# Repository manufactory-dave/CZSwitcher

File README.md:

# CZSwitcher

====Cube Zero Switcher Project Version 2 Alpha====

Version 2 alpha
Board revisions:

Distro Rev [tbc]
Carriage Rev [tbc]
Tool Rev [tbc]

====Changelog====

[fix V1 errors]
Add ADXL345 to carriage board
Upgrade files to KiCad V6
Integrate files into one project [maybe]

====Cube Zero Overview====

Cube Zero is a CoreXY tool changing 3D printer design that is currently WIP. The requirements for the machine are:
- The machine shall have high rigidity
- The machine should be readily adaptable to use a heated enclosure
- The machine must be electrically safe
- The machine must use CoreXY architecture
- The design should minimise moving mass
- The machine shall support multi-material prints
- The machine should have rapidly changeable tools to enable rapid swap reliability
- The machine should not be reliant on a specific firmware

These requirements have evolved with the design, currently the design is a CoreXY machine with 3 tool changer stations. Currently the design utilises direct drive extruders using Nema10 motors and a worm gear arrangement to minimise mass. Hot end compatibiliy is to be E3D groovemount.

Why choose the name Cube Zero? Because that film came after Cube 2 Hypercube, and it was a better film.

====Custom Electronics Overview (This repository)====

The drive to minimise mass (and the potential for tangling with 3 or more tools all with separate cable trains to be independently strain relieved and managed leads to the chosen solution: Independent wiring to tool storage bays and the toolhead, with a single flexible flat cable (FFC) connecting the toolhead.
A wide FFC is capable of supporting its own mass and is very light, and furthermore is flexible in two axis simultaneously, making it substantially simpler and more robust than multiple cable chains, at the cost of requiring breakout PCBs.
By selecting a suitably heavy duty FFC (Samtec manufacture high current capacity cables) and using multiple conductors for the heater, 5A current capacity for heaters is easily achieved.
The result of using hot swapped tools is that a single stepper driver can be  used to control every extruder, meaning that any 4 driver board could theoretically handle an arbitrary number of tools.

The system architecture creates the need for several circuit boards having the following requirements:
- The electronics must connect the printer control board to the docking stations and toolhead
- Sensor, motor and heater connections should be switched in a low latency, low resistance manner
- Tool docks must have temperature sense and heater connections
- The toolhead should support auxilliary functions such as part cooling fans, servo motors and bed levelling sensors
- The toolhead should support ADXL345 integration for Klipper Input Shaper operation

[edited up to here]

Three seperate KiCad v5 projects are stored here:

Distroboard: The heart of the electronics - this takes a common stepper motor input and 3 separate fan/heater/thermistor channels, bed probing and well as 3 auxilliary channels and routes them to a 20 way 1mm pitch FFC.
Designed to interface with a Bigtreetech GTR V1.0, but will probably work with other boards, YMMV.

*Current Ratings*
Heaters - 3.5A per channel, max 30V
Fans - 1A per channel, routed via Aux 1
Auxilliary channels - 1A per channel, max 24V
Thermistors - currently designed to interface directly with the GTR thermistors. A 3V3 connection is required for at least one thermistor as this supplies power to your Z probe solution of choice.
	Provision has been made to allow these channels to drive thermocouple or PTH amplifiers.
5V in - 1A max
VDC in - 1A max, 30V max
Stepper motor - designed for a TMC2209, with protection circuitry for hot swapping taken from the TMC2209 datasheet. This is not intended and disable stepper commands should be used before swapping motors, however the protection is there just in case.
Probe - low current.

Carriageboard: 3 separate boards.

Carriage Board A:
Breaks out the FFC cable into the 3 aux outputs, a BLTouch connector, an interface for a Precision Piezo V2.85 board and 2 piezo inputs, status LEDs for the heater and probe throughput.

Carriage Board B:
Interfaces with toolhead, provides 2 aux outputs, and repeats status LEDs

LED status board:
For if you need status LEDs somewhere that the above two boards don't help with.

Toolboard: 5 separate boards:
Toolboard A & B ride on the tool, and provide electrical connection to the toolhead and dock. Everything that needs to terminate here to support extruder motors, hot end cooling fans, thermal sense and heating, terminates here.

Dock Interface Board - Takes a high power and data connection from the Distro board, takes a logic input from an external sensor that detects when a tool is removed from the dock and sends it down the data connection to enable that tool over the FFC
Dock LEDs - provides heating and tool select status LEDs for fun/info/making your machine look cool.
Dock Umbilical - connected via FFC to the interface board, provides a mobile connection point to form electrical connections with a docked tool.

====Errors====
There are two known errors:
Carriageboard (no gate resistor on Q2)
Toolboard (Q2 Source and Drain reversed)

====BOM====
The BOM is sketchy, once it's defined and working I'll update it. For now it has several errors and parts I already owned do not have part numbers attached.

====PCBs====
Not available at this time

====Version History====

Version 1
Board revisions:

Distro Rev 0
Carriage Rev 0
Tool Rev 0

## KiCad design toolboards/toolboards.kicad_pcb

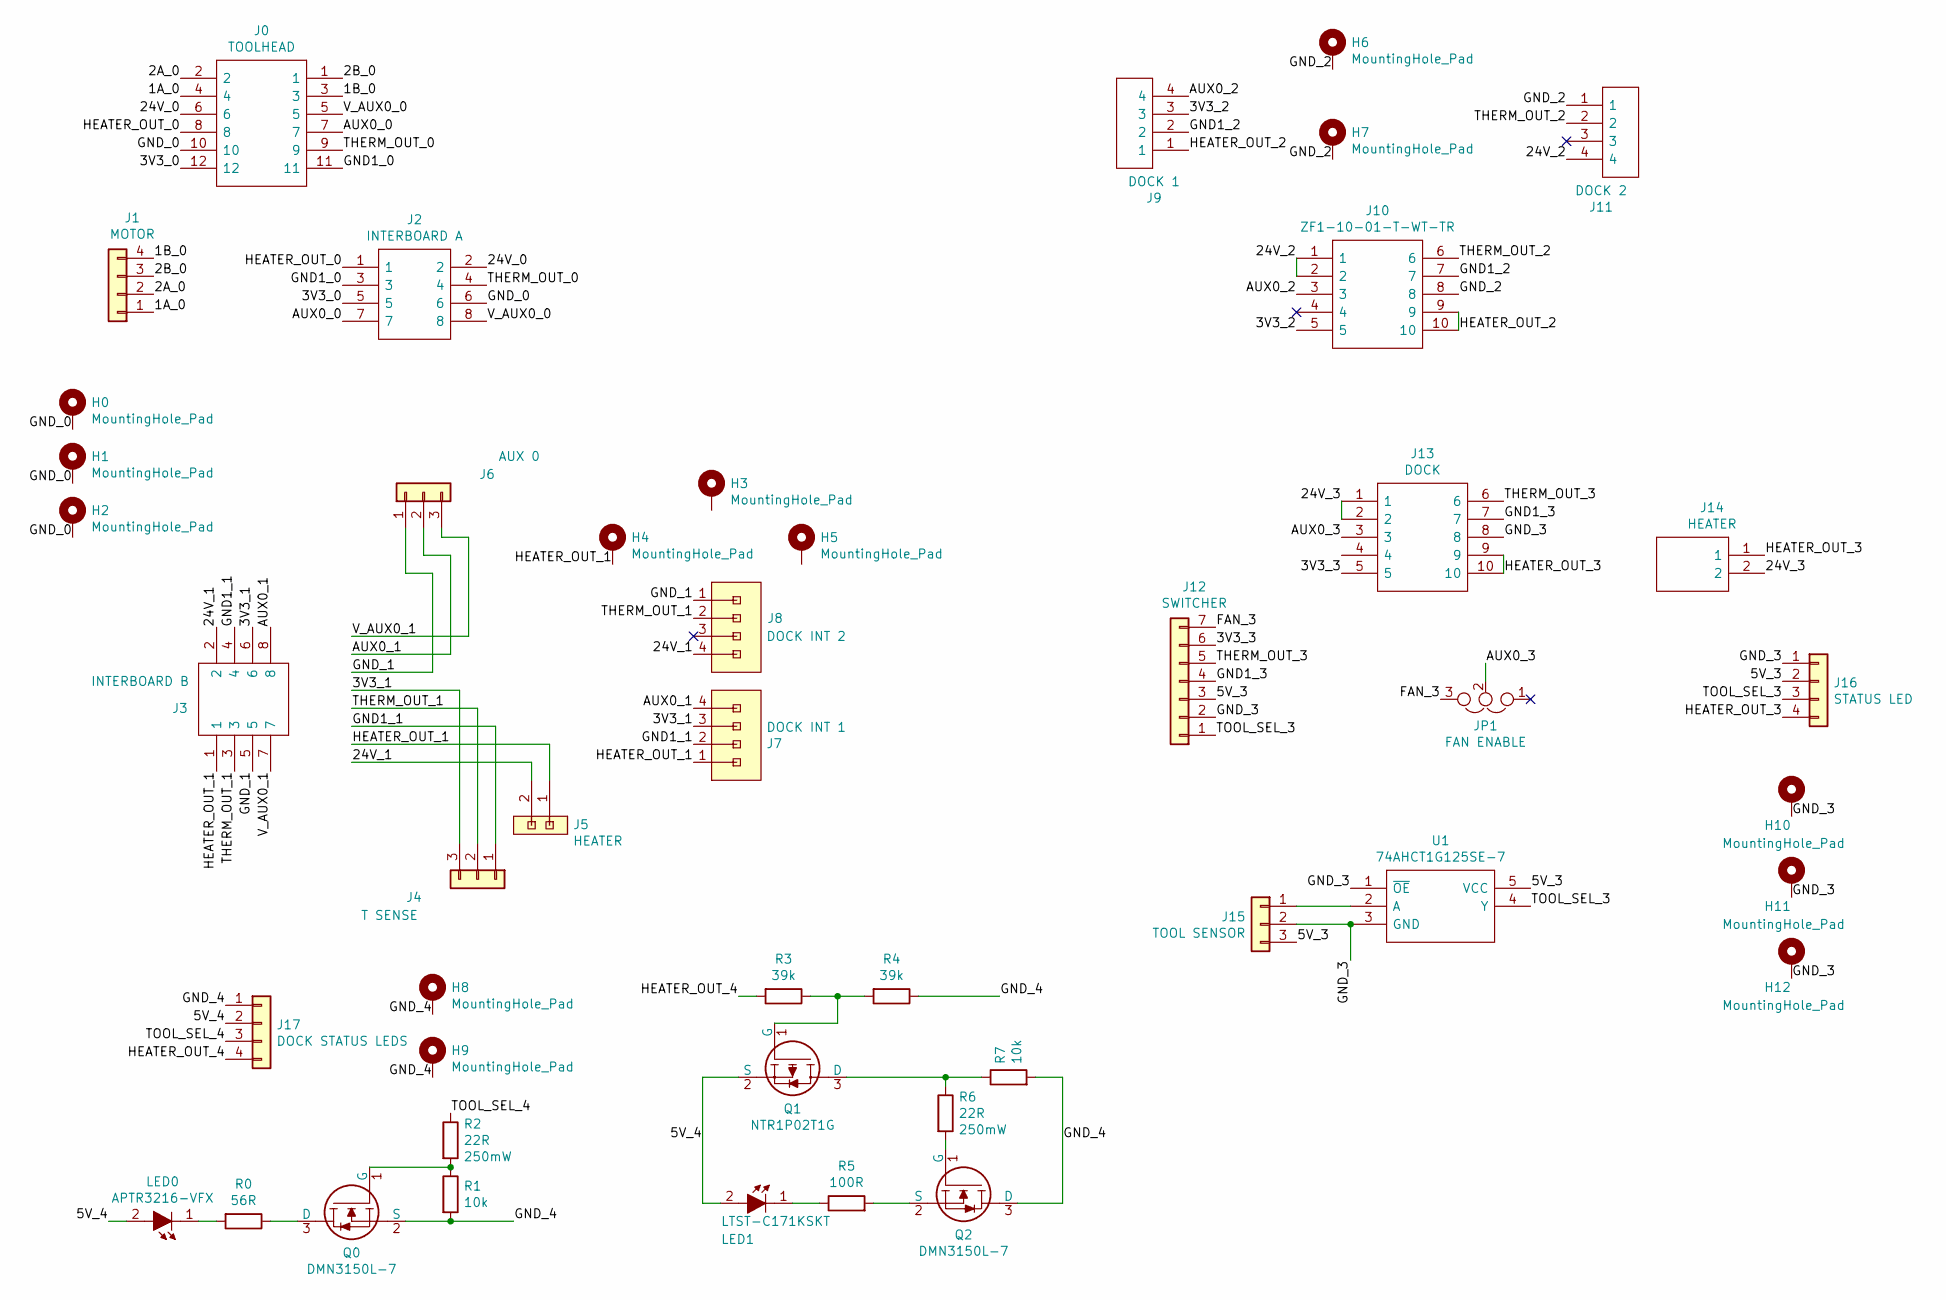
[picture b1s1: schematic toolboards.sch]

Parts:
H0, H1, H2, H3, H4, H5: MountingHole_Pad; MountingHole_2.7mm_M2.5_DIN965_Pad_TopBottom
H6, H7, H8, H9, H10, H11, H12: MountingHole_Pad; MountingHole_3.2mm_M3_DIN965_Pad_TopBottom
J0: TOOLHEAD; 8021001230507101_HS; Manufacturer_Part_Number 802-10-012-30-507101
J1: MOTOR; JST_XH_B4B-XH-A_1x04_P2.50mm_Vertical
J2: INTERBOARD A; HDRV8W64P254_2X4_1016X495X838P; Manufacturer_Part_Number TSW-104-07-T-D
J3: INTERBOARD B; SSW-104-XX-YYY-D-RA; Manufacturer_Part_Number SSW-104-02-T-D-RA
J4: T SENSE; JST-XH_2.50MM_03x01_SMT; Manufacturer_Part_Number S3B-XH-SM4-TB(LF)(SN)
J5, J14: HEATER; SHDRRA2W102P0X508_1X2_1016X1200X850P; Manufacturer_Part_Number 282815-2
J6: AUX 0; JST-XH_2.50MM_03x01_SMT; Manufacturer_Part_Number S3B-XH-SM4-TB(LF)(SN)
J7: DOCK INT 1; 8MM11000402131_handsolder
J8: DOCK INT 2; 8MM11000402131_handsolder
J9: DOCK 1; 811-S1-004-10-017101; Mouser Part Number 437-8MM11000402131
J10: ZF1-10-01-T-WT-TR; ZF1-10-XX-ZZ-WT_Handsolder; Manufacturer_Part_Number ZF1-10-01-T-WT-TR
J11: DOCK 2; 811-S1-004-10-017101; Mouser Part Number 437-8MM11000402131
J12: SWITCHER; JST_XH_B7B-XH-A_1x07_P2.50mm_Vertical
J13: DOCK; ZF1-10-XX-ZZ-WT_Handsolder; Manufacturer_Part_Number ZF1-10-01-T-WT-TR
J15: TOOL SENSOR; JST_XH_B3B-XH-A_1x03_P2.50mm_Vertical
J16: STATUS LED; JST-ZH_S4B-ZR-SM4A-TF; Part Number S4B-ZR-SM4A-TF
J17: DOCK STATUS LEDS; JST-ZH_S4B-ZR-SM4A-TF; Part Number S4B-ZR-SM4A-TF
JP1: FAN ENABLE; PinHeader_1x03_P2.54mm_Vertical
LED0: APTR3216-VFX; LED_1206_3216Metric_Pad1.42x1.75mm_HandSolder; Manufacturer_Part_Number APTR3216-VFX
LED1: LTST-C171KSKT; LED_0805_2012Metric_Pad1.15x1.40mm_HandSolder; Manufacturer_Part_Number LTST-C171KSKT
Q0, Q2: DMN3150L-7; SUPER-SOT-3; Manufacturer_Part_Number DMN3150L-7
Q1: NTR1P02T1G; SUPER-SOT-3; Manufacturer_Part_Number NTR1P02T1G
R0: 56R; R_0805_2012Metric_Pad1.20x1.40mm_HandSolder; Manufacturer_Part_Number RK73B2ATTD560J
R1, R7: 10k; R_0805_2012Metric_Pad1.20x1.40mm_HandSolder; Manufacturer_Part_Number RK73B2ATTE103J
R2, R6: 22R; R_0805_2012Metric_Pad1.20x1.40mm_HandSolder; Manufacturer_Part_Number RK73B2ATTDD220J
R3: 39k; R_0805_2012Metric_Pad1.20x1.40mm_HandSolder; Manufacturer_Part_Number RK73B2ATTE393J
R4: 39k; R_0805_2012Metric_Pad1.20x1.40mm_HandSolder; Manufacturer_Part_Number RK73B2ATTE103J
R5: 100R; R_0805_2012Metric_Pad1.20x1.40mm_HandSolder; Manufacturer_Part_Number RK73B2ATTE101J
U1: 74AHCT1G125SE-7; SOT-23-5_HandSoldering; Manufacturer_Part_Number 74AHCT1G125SE-7

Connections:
/1A_0: J0.4, J1.1
/1B_0: J0.3, J1.4
/2A_0: J0.2, J1.2
/2B_0: J0.1, J1.3
/3V3_0: J0.12, J2.5
/3V3_1: J3.6, J4.3, J7.3
/3V3_2: J9.3, J10.5
/3V3_3: J12.6, J13.5
/5V_3: J12.3, J15.3, J16.2, U1.5 (VCC)
/5V_4: J17.2, LED0.2, LED1.2, Q1.2 (S)
/24V_0: J0.6, J2.2
/24V_1: J3.2, J4.4, J4.5, J5.2, J8.4
/24V_2: J10.1, J10.2, J11.4
/24V_3: J13.1, J13.2, J14.2
/AUX0_0: J0.7, J2.7
/AUX0_1: J3.8, J6.2, J7.4
/AUX0_2: J9.4, J10.3
/AUX0_3: J13.3, JP1.2
/FAN_3: J12.7, JP1.3
/GND1_0: J0.11, J2.3
/GND1_1: J3.4, J4.1, J7.2
/GND1_2: J9.2, J10.7
/GND1_3: J12.4, J13.7
/GND_0: H0.1, H1.1, H2.1, J0.10, J2.6
/GND_1: J3.5, J6.1, J8.1
/GND_2: H6.1, H7.1, J10.8, J10.11, J10.12, J11.1
/GND_3: H10.1, H11.1, H12.1, J12.2, J13.8, J15.2, J16.1, U1.1 (~OE), U1.3 (GND)
/GND_4: H8.1, H9.1, J17.1, Q0.2 (S), Q2.3 (D), R1.2, R4.1, R7.2
/HEATER_OUT_0: J0.8, J2.1
/HEATER_OUT_1: H4.1, J3.1, J5.1, J7.1
/HEATER_OUT_2: J9.1, J10.9, J10.10
/HEATER_OUT_3: J13.9, J13.10, J14.1, J16.4
/HEATER_OUT_4: J17.4, R3.2
/THERM_OUT_0: J0.9, J2.4
/THERM_OUT_1: J3.3, J4.2, J8.2
/THERM_OUT_2: J10.6, J11.2
/THERM_OUT_3: J12.5, J13.6
/TOOL_SEL_3: J12.1, J16.3, U1.4 (Y)
/TOOL_SEL_4: J17.3, R2.1
/V_AUX0_0: J0.5, J2.8
/V_AUX0_1: J3.7, J6.3
unnamed: J15.1, U1.2 (A)
unnamed: LED0.1, R0.2
unnamed: LED1.1, R5.1
unnamed: Q0.1 (G), R1.1, R2.2
unnamed: Q0.3 (D), R0.1
unnamed: Q1.1 (G), R3.1, R4.2
unnamed: Q1.3 (D), R6.1, R7.1
unnamed: Q2.1 (G), R6.2
unnamed: Q2.2 (S), R5.2

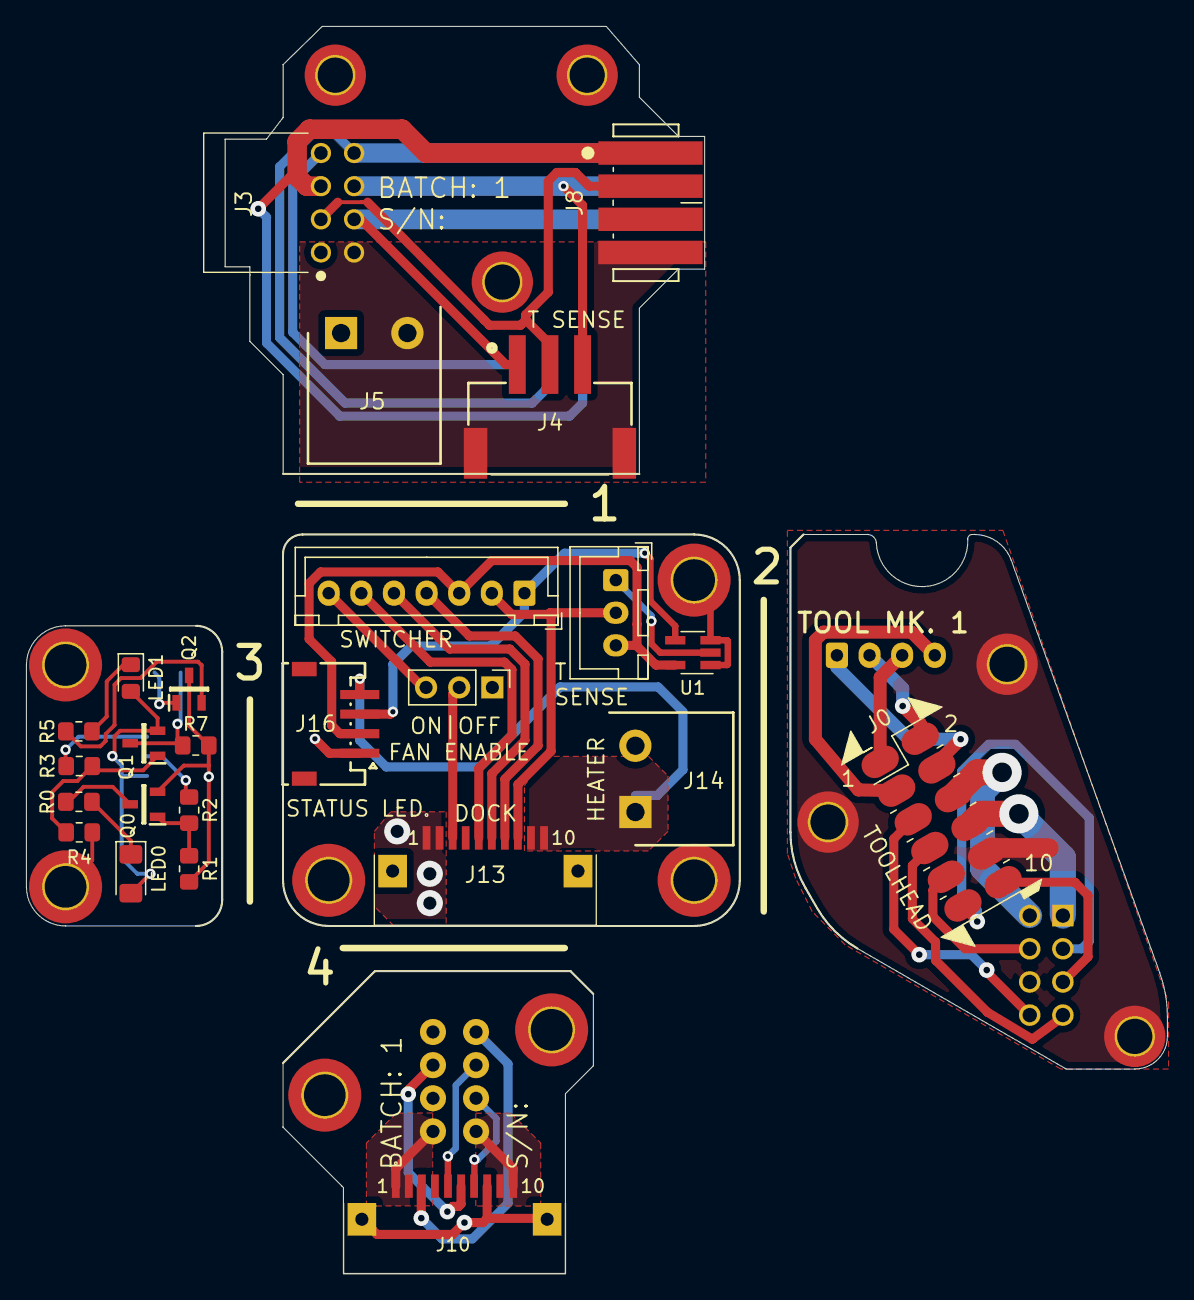
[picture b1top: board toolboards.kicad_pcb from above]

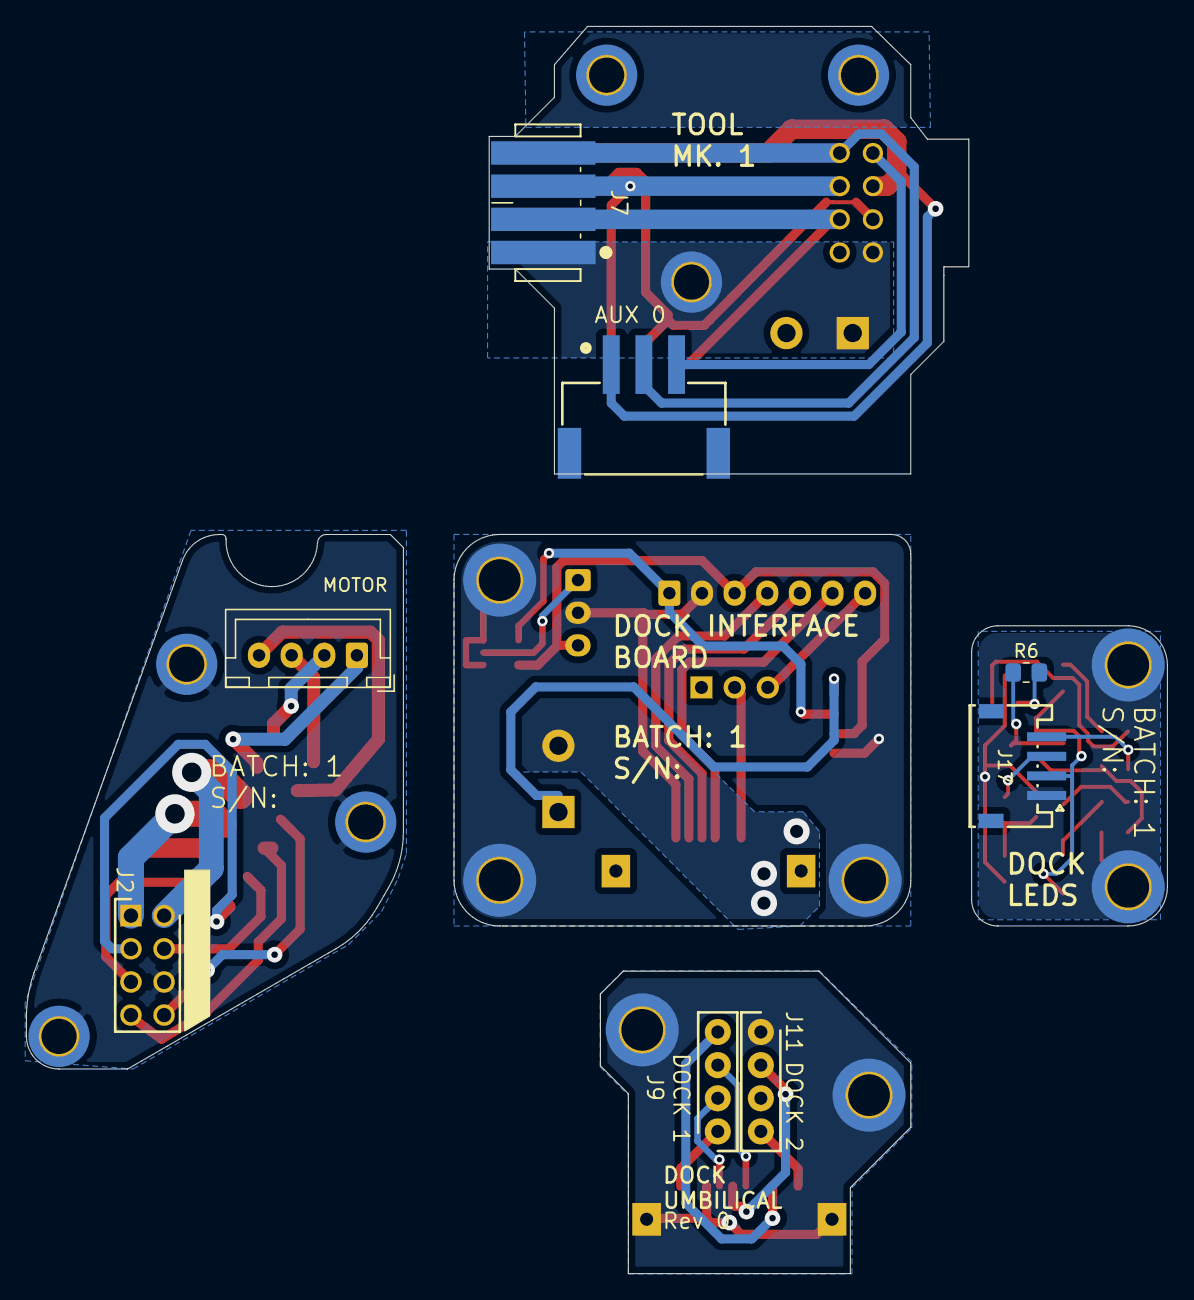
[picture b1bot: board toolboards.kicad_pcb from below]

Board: 2 copper layers, 87.4 x 95.6 mm, 46 parts (8 on the bottom side), 50 nets.

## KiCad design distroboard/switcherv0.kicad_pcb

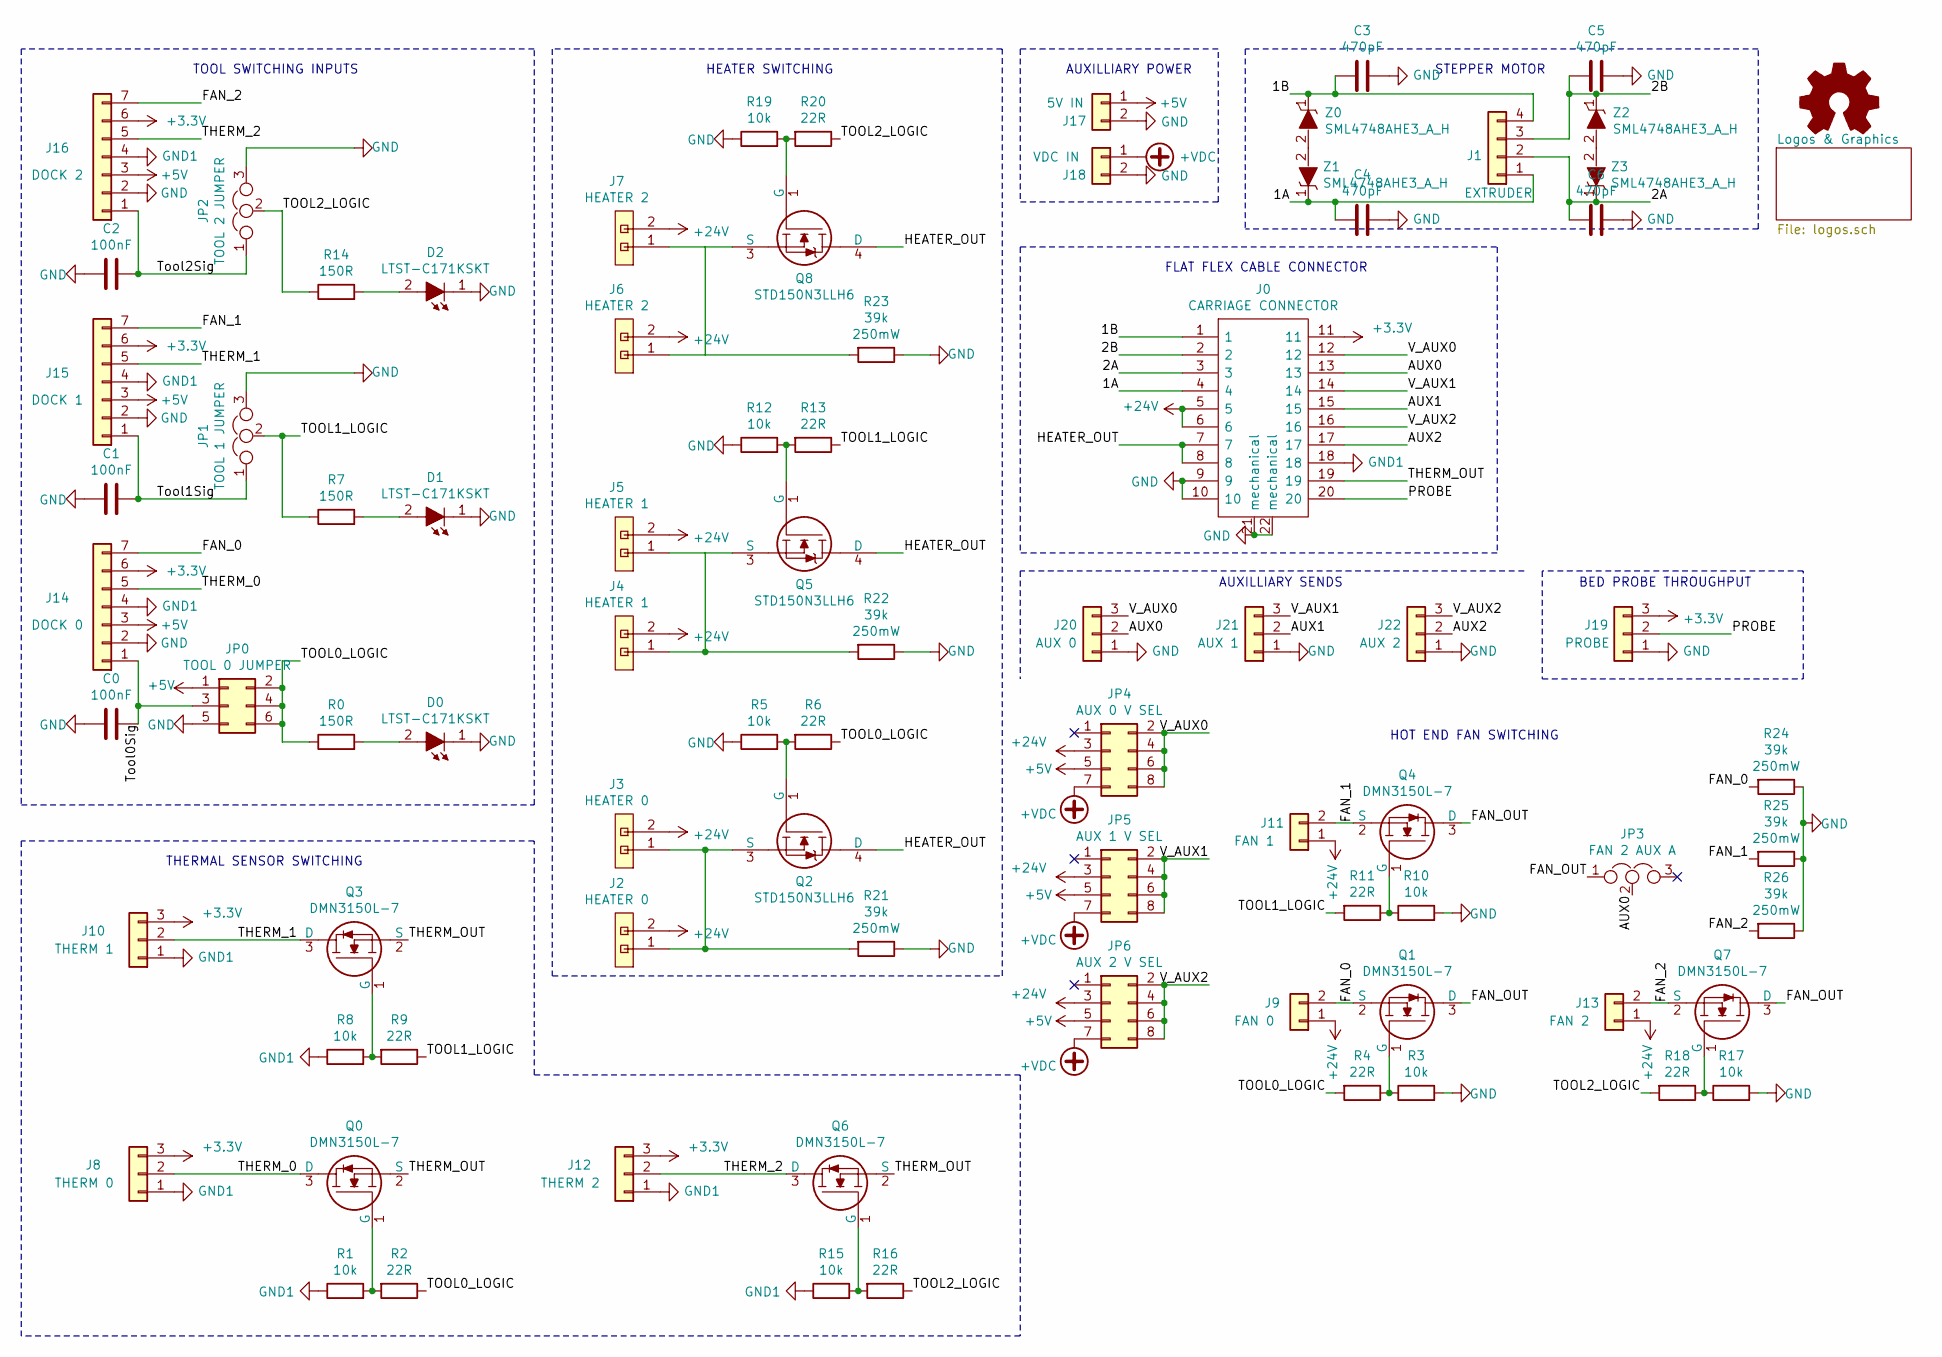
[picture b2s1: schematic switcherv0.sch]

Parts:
C0, C1, C2: 100nF; C_0805_2012Metric_Pad1.18x1.45mm_HandSolder; Manufacturer_Part_Number 08051C103KAT2A
C3, C4, C5, C6: 470pF; C_0805_2012Metric_Pad1.18x1.45mm_HandSolder; Manufacturer_Part_Number C0805C471J1GACTU
D0, D1, D2: LTST-C171KSKT; LED_0805_2012Metric_Pad1.15x1.40mm_HandSolder; Manufacturer_Part_Number LTST-C171KSKT
J0: CARRIAGE CONNECTOR; ZF1-20-XX-ZZ-WT; Manufacturer_Part_Number ZF1-20-01-T-WT
J1: EXTRUDER; JST_XH_B4B-XH-A_1x04_P2.50mm_Vertical
J2, J3: HEATER 0; SHDR2W102P0X508_1X2_1016X835X1230P; Manufacturer_Part_Number 282824-2
J4, J5: HEATER 1; SHDR2W102P0X508_1X2_1016X835X1230P; Manufacturer_Part_Number 282824-2
J6, J7: HEATER 2; SHDR2W102P0X508_1X2_1016X835X1230P; Manufacturer_Part_Number 282824-2
J8: THERM 0; JST_XH_B3B-XH-A_1x03_P2.50mm_Vertical
J9: FAN 0; JST_XH_B2B-XH-A_1x02_P2.50mm_Vertical
J10: THERM 1; JST_XH_B3B-XH-A_1x03_P2.50mm_Vertical
J11: FAN 1; JST_XH_B2B-XH-A_1x02_P2.50mm_Vertical
J12: THERM 2; JST_XH_B3B-XH-A_1x03_P2.50mm_Vertical
J13: FAN 2; JST_XH_B2B-XH-A_1x02_P2.50mm_Vertical
J14: DOCK 0; JST_XH_B7B-XH-A_1x07_P2.50mm_Vertical
J15: DOCK 1; JST_XH_B7B-XH-A_1x07_P2.50mm_Vertical
J16: DOCK 2; JST_XH_B7B-XH-A_1x07_P2.50mm_Vertical
J17: 5V IN; JST_XH_B2B-XH-A_1x02_P2.50mm_Vertical
J18: VDC IN; JST_XH_B2B-XH-A_1x02_P2.50mm_Vertical
J19: PROBE; JST_XH_B3B-XH-A_1x03_P2.50mm_Vertical
J20: AUX 0; JST_XH_B3B-XH-A_1x03_P2.50mm_Vertical
J21: AUX 1; JST_XH_B3B-XH-A_1x03_P2.50mm_Vertical
J22: AUX 2; JST_XH_B3B-XH-A_1x03_P2.50mm_Vertical
JP0: TOOL 0 JUMPER; PinHeader_2x03_P2.54mm_Vertical
JP1: TOOL 1 JUMPER; PinHeader_1x03_P2.54mm_Vertical
JP2: TOOL 2 JUMPER; PinHeader_1x03_P2.54mm_Vertical
JP3: FAN 2 AUX A; PinHeader_1x03_P2.54mm_Vertical
JP4: AUX 0 V SEL; PinHeader_2x04_P1.27mm_Vertical; Manufacturer_Part_Number M50-055023W0445
JP5: AUX 1 V SEL; PinHeader_2x04_P1.27mm_Vertical; Manufacturer_Part_Number M50-055023W0445
JP6: AUX 2 V SEL; PinHeader_2x04_P1.27mm_Vertical; Manufacturer_Part_Number M50-055023W0445
LOGO2: Logo_Open_Hardware_Small; OSHW-Symbol_8.9x8mm_Copper
Q0, Q1, Q3, Q4, Q6, Q7: DMN3150L-7; SUPER-SOT-3; Manufacturer_Part_Number DMN3150L-7
Q2, Q5, Q8: STD150N3LLH6; TO228P972X240-3N; Manufacturer_Part_Number STD150N3LLH6
R0, R7, R14: 150R; R_0805_2012Metric_Pad1.20x1.40mm_HandSolder; Manufacturer_Part_Number RK73B2ATTE151J
R1, R3, R5, R8, R10, R12, R15, R17, R19: 10k; R_0805_2012Metric_Pad1.20x1.40mm_HandSolder; Manufacturer_Part_Number RK73B2ATTE103J
R2, R4, R6, R9, R11, R13, R16, R18, R20: 22R; R_0805_2012Metric_Pad1.20x1.40mm_HandSolder; Manufacturer_Part_Number RK73B2ATTDD220J
R21, R22, R23, R24, R25, R26: 39k; R_0805_2012Metric_Pad1.20x1.40mm_HandSolder; Manufacturer_Part_Number RK73B2ATTD393J
Z0, Z1, Z2, Z3: SML4748AHE3_A_H; DIOM5127X229N; Mouser Part Number 78-SML4748AHE3_A/H

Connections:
+3V3: J0.11, J8.3, J10.3, J12.3, J14.6, J15.6, J16.6, J19.3
+5V: J14.3, J15.3, J16.3, J17.1, JP0.1, JP4.5, JP5.5, JP6.5
+24V: J0.5, J0.6, J2.2, J3.2, J4.2, J5.2, J6.2, J7.2, J9.1, J11.1, J13.1, JP4.3, JP5.3, JP6.3
+VDC: J18.1, JP4.7, JP5.7, JP6.7
/1A: C4.2, J0.4, J1.1, Z1.1
/1B: C3.2, J0.1, J1.4, Z0.1
/2A: C6.2, J0.3, J1.2, Z3.1
/2B: C5.2, J0.2, J1.3, Z2.1
/AUX0: J0.13, J20.2, JP3.2
/AUX1: J0.15, J21.2
/AUX2: J0.17, J22.2
/FAN_0: J9.2, J14.7, Q1.2 (S), R24.2
/FAN_1: J11.2, J15.7, Q4.2 (S), R25.2
/FAN_2: J13.2, J16.7, Q7.2 (S), R26.2
/FAN_OUT: JP3.1, Q1.3 (D), Q4.3 (D), Q7.3 (D)
/HEATER_OUT: J0.7, J0.8, Q2.4 (D), Q5.4 (D), Q8.4 (D)
/PROBE: J0.20, J19.2
/THERM_0: J8.2, J14.5, Q0.3 (D)
/THERM_1: J10.2, J15.5, Q3.3 (D)
/THERM_2: J12.2, J16.5, Q6.3 (D)
/THERM_OUT: J0.19, Q0.2 (S), Q3.2 (S), Q6.2 (S)
/TOOL0_LOGIC: JP0.2, JP0.4, JP0.6, R0.1, R2.1, R4.2, R6.1
/TOOL1_LOGIC: JP1.2, R7.1, R9.1, R11.2, R13.1
/TOOL2_LOGIC: JP2.2, R14.1, R16.1, R18.2, R20.1
/Tool0Sig: C0.1, J14.1, JP0.3
/Tool1Sig: C1.1, J15.1, JP1.1
/Tool2Sig: C2.1, J16.1, JP2.1
/V_AUX0: J0.12, J20.3, JP4.2, JP4.4, JP4.6, JP4.8
/V_AUX1: J0.14, J21.3, JP5.2, JP5.4, JP5.6, JP5.8
/V_AUX2: J0.16, J22.3, JP6.2, JP6.4, JP6.6, JP6.8
GND: C0.2, C1.2, C2.2, C3.1, C4.1, C5.1, C6.1, D0.1, D1.1, D2.1, J0.9, J0.10, J0.21 (mechanical), J0.22 (mechanical), J14.2, J15.2, J16.2, J17.2, J18.2, J19.1, J20.1, J21.1, J22.1, JP0.5, JP1.3, JP2.3, R3.2, R5.1, R10.2, R12.1, R17.2, R19.1, R21.1, R22.1, R23.1, R24.1, R25.1, R26.1; also elsewhere on the board
GND1: J0.18, J8.1, J10.1, J12.1, J14.4, J15.4, J16.4, R1.1, R8.1, R15.1
unnamed: D0.2, R0.2
unnamed: D1.2, R7.2
unnamed: D2.2, R14.2
unnamed: J2.1, J3.1, Q2.3 (S), R21.2
unnamed: J4.1, J5.1, Q5.3 (S), R22.2
unnamed: J6.1, J7.1, Q8.3 (S), R23.2
unnamed: Q0.1 (G), R1.2, R2.2
unnamed: Q1.1 (G), R3.1, R4.1
unnamed: Q2.1 (G), R5.2, R6.2
unnamed: Q3.1 (G), R8.2, R9.2
unnamed: Q4.1 (G), R10.1, R11.1
unnamed: Q5.1 (G), R12.2, R13.2
unnamed: Q6.1 (G), R15.2, R16.2
unnamed: Q7.1 (G), R17.1, R18.1
unnamed: Q8.1 (G), R19.2, R20.2
unnamed: Z0.2, Z1.2
unnamed: Z2.2, Z3.2

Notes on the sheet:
TOOL SWITCHING INPUTS
HEATER SWITCHING
THERMAL SENSOR SWITCHING
AUXILLIARY POWER
FLAT FLEX CABLE CONNECTOR
AUXILLIARY SENDS
BED PROBE THROUGHPUT
HOT END FAN SWITCHING
STEPPER MOTOR

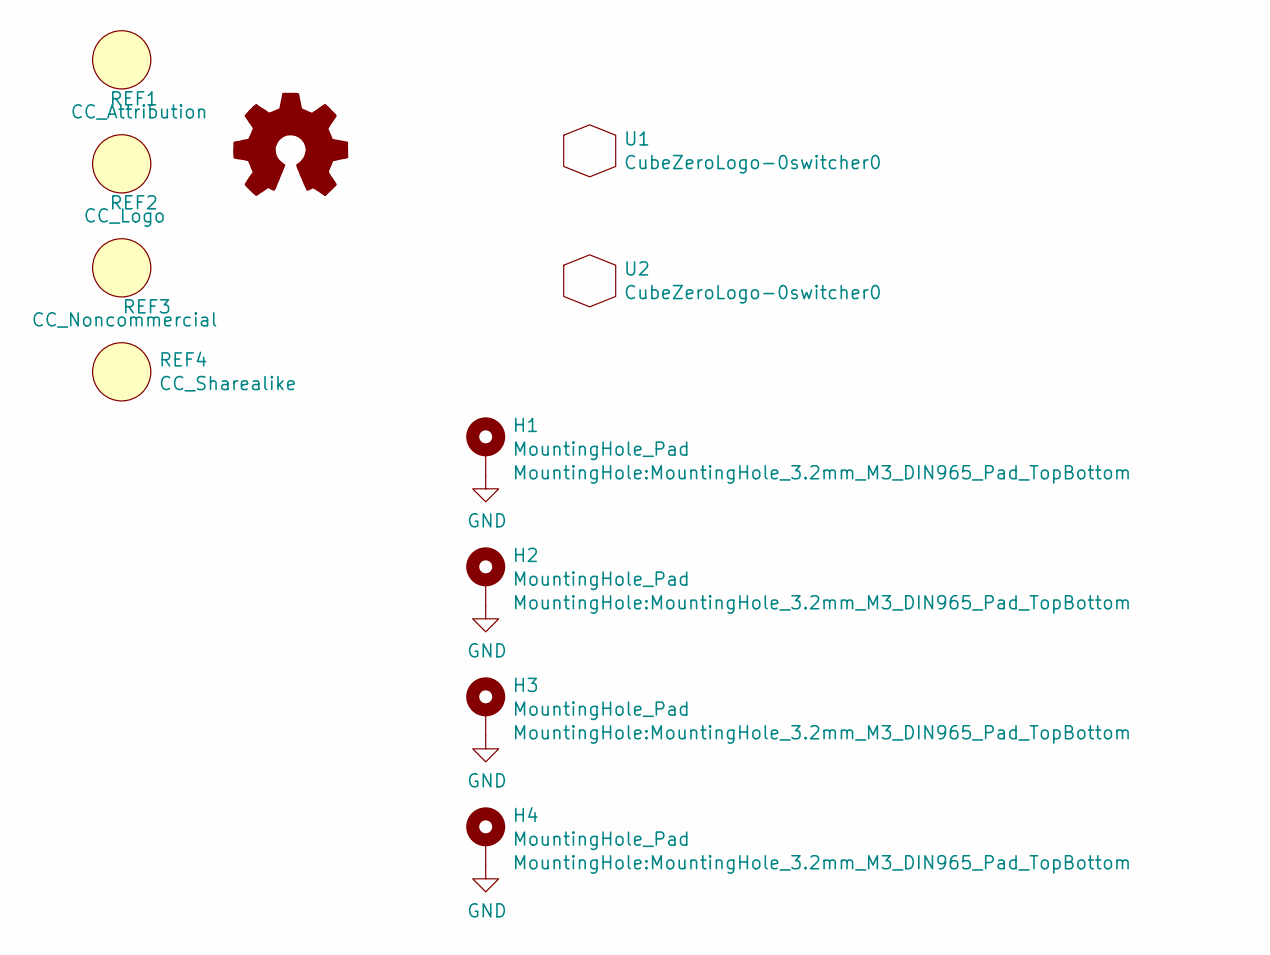
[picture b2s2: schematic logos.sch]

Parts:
H1, H2, H3, H4: MountingHole_Pad; MountingHole_3.2mm_M3_DIN965_Pad_TopBottom
LOGO1: Logo_Open_Hardware_Small; OSHW-Logo_11.4x12mm_SilkScreen
REF1: CC_Attribution; Symbol_CC-Attribution_Silkscreen_Small
REF2: CC_Logo; Symbol_CC_Logo_Silkscreen_small
REF3: CC_Noncommercial; Symbol_CC-Noncommercial_Silkscreen_Small
REF4: CC_Sharealike; Symbol_CC-ShareAlike_Silkscreen_Small
U1: CubeZeroLogo-0switcher0; CubeZeroLogo_Ink_And_Cu
U2: CubeZeroLogo-0switcher0; CubeZeroLogo_Silk

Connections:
GND: H1.1, H2.1, H3.1, H4.1; also elsewhere on the board

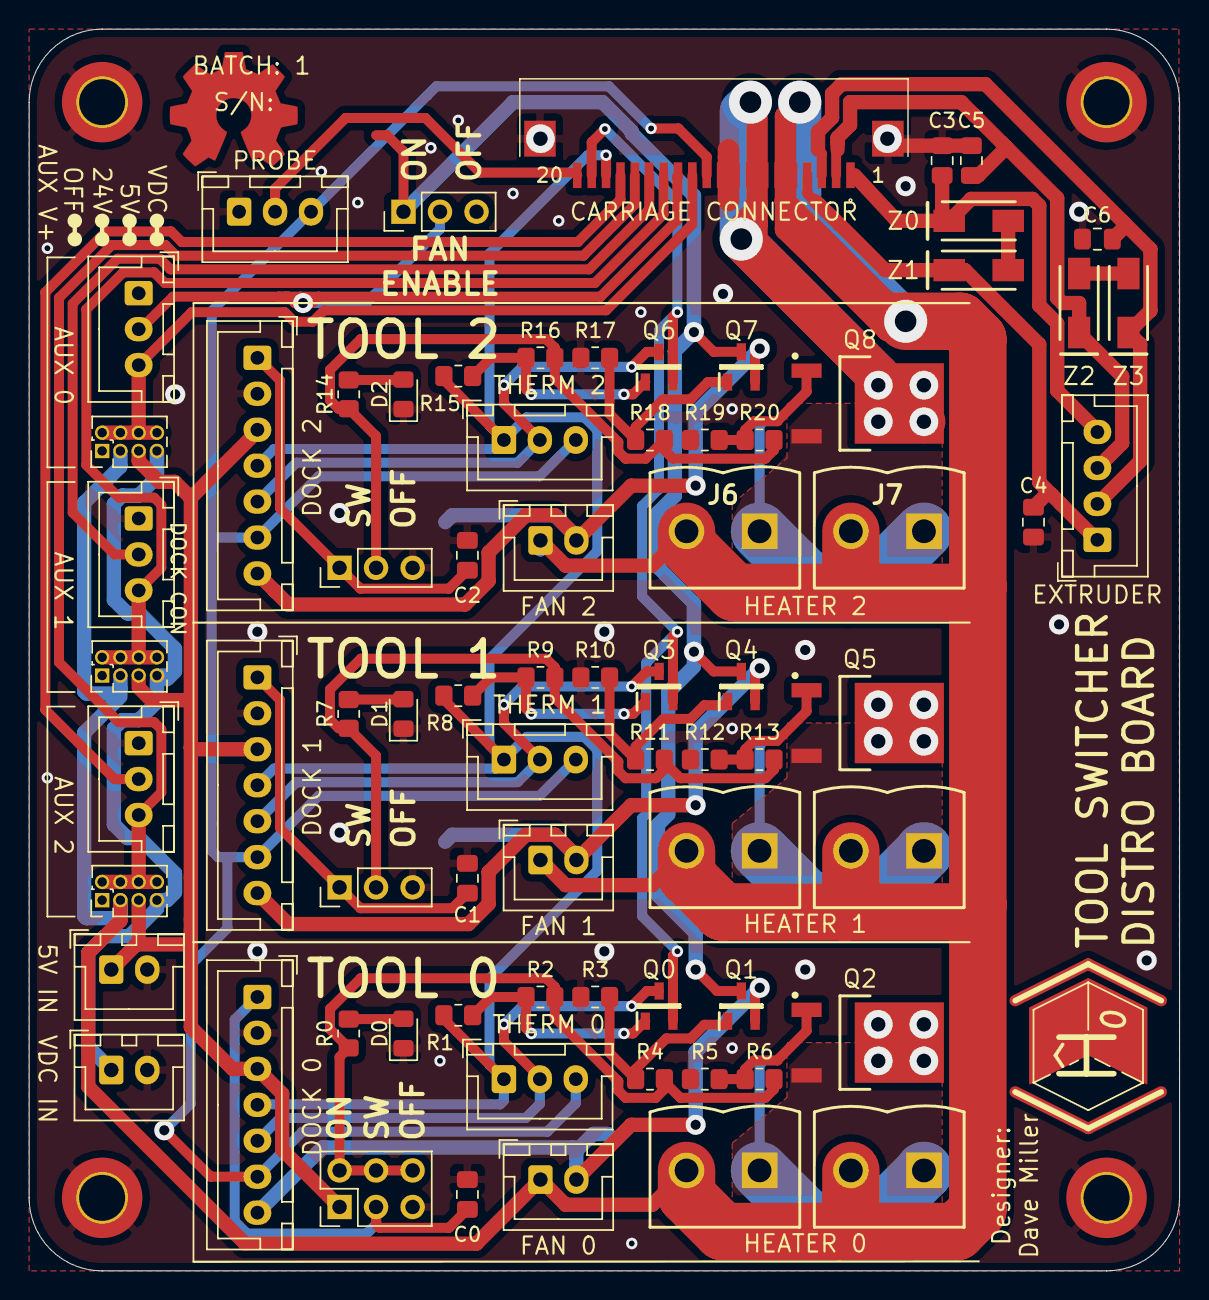
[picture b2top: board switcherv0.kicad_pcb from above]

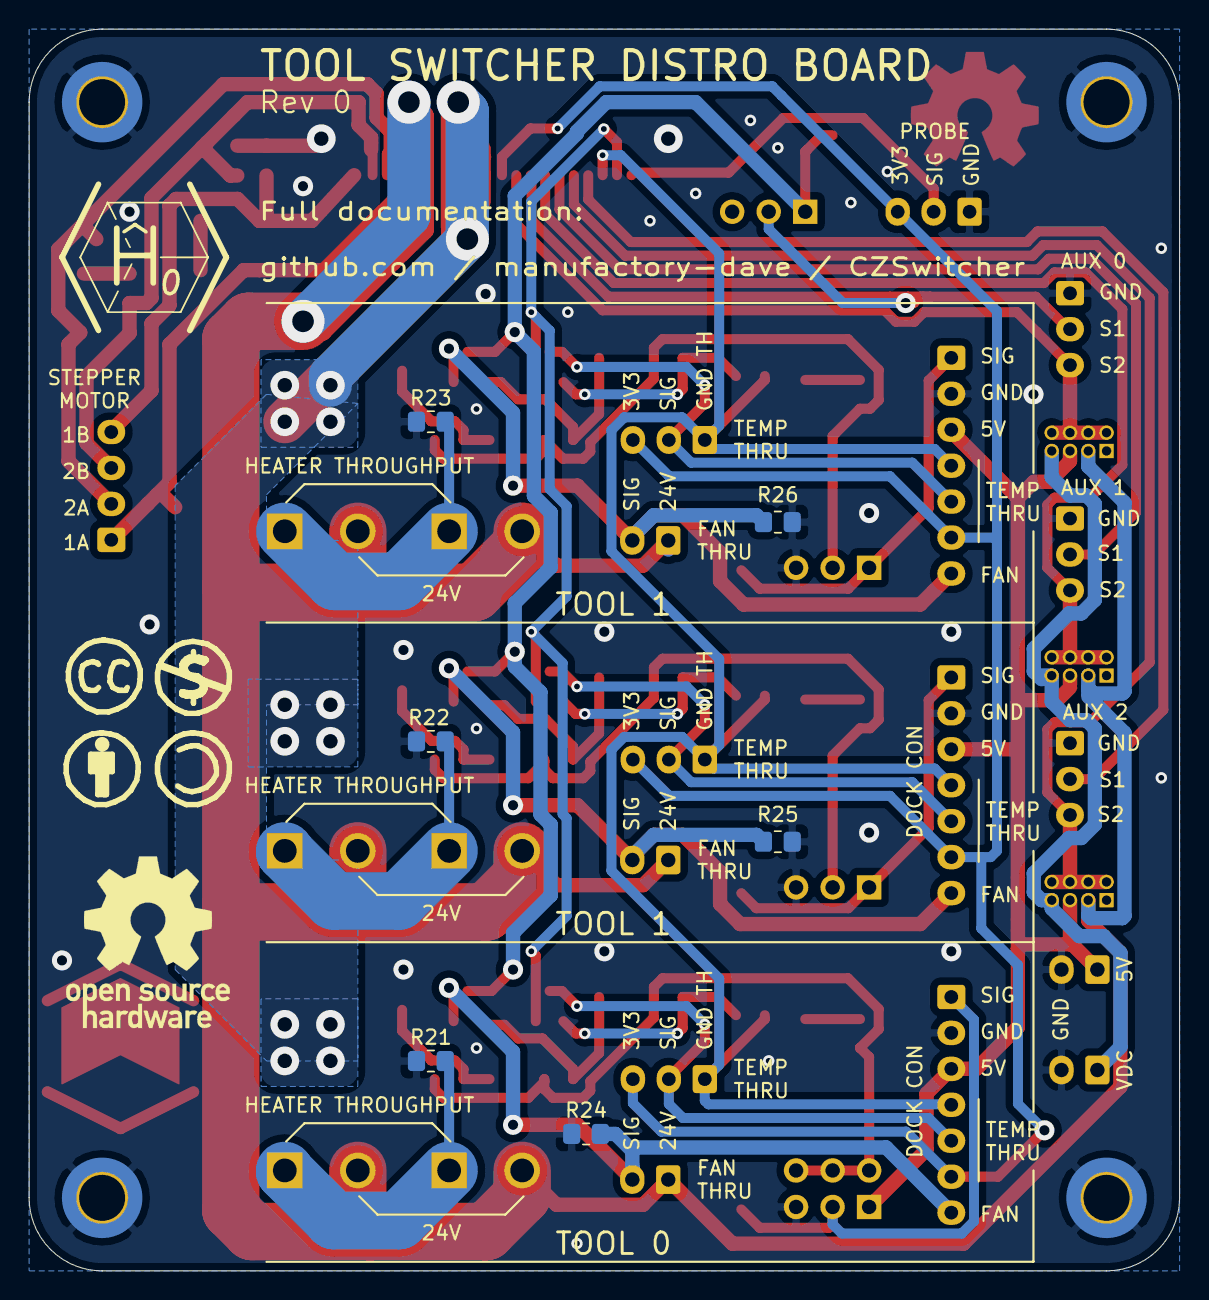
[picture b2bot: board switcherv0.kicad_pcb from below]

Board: 2 copper layers, 80.0 x 86.4 mm, 92 parts (12 on the bottom side), 49 nets.
